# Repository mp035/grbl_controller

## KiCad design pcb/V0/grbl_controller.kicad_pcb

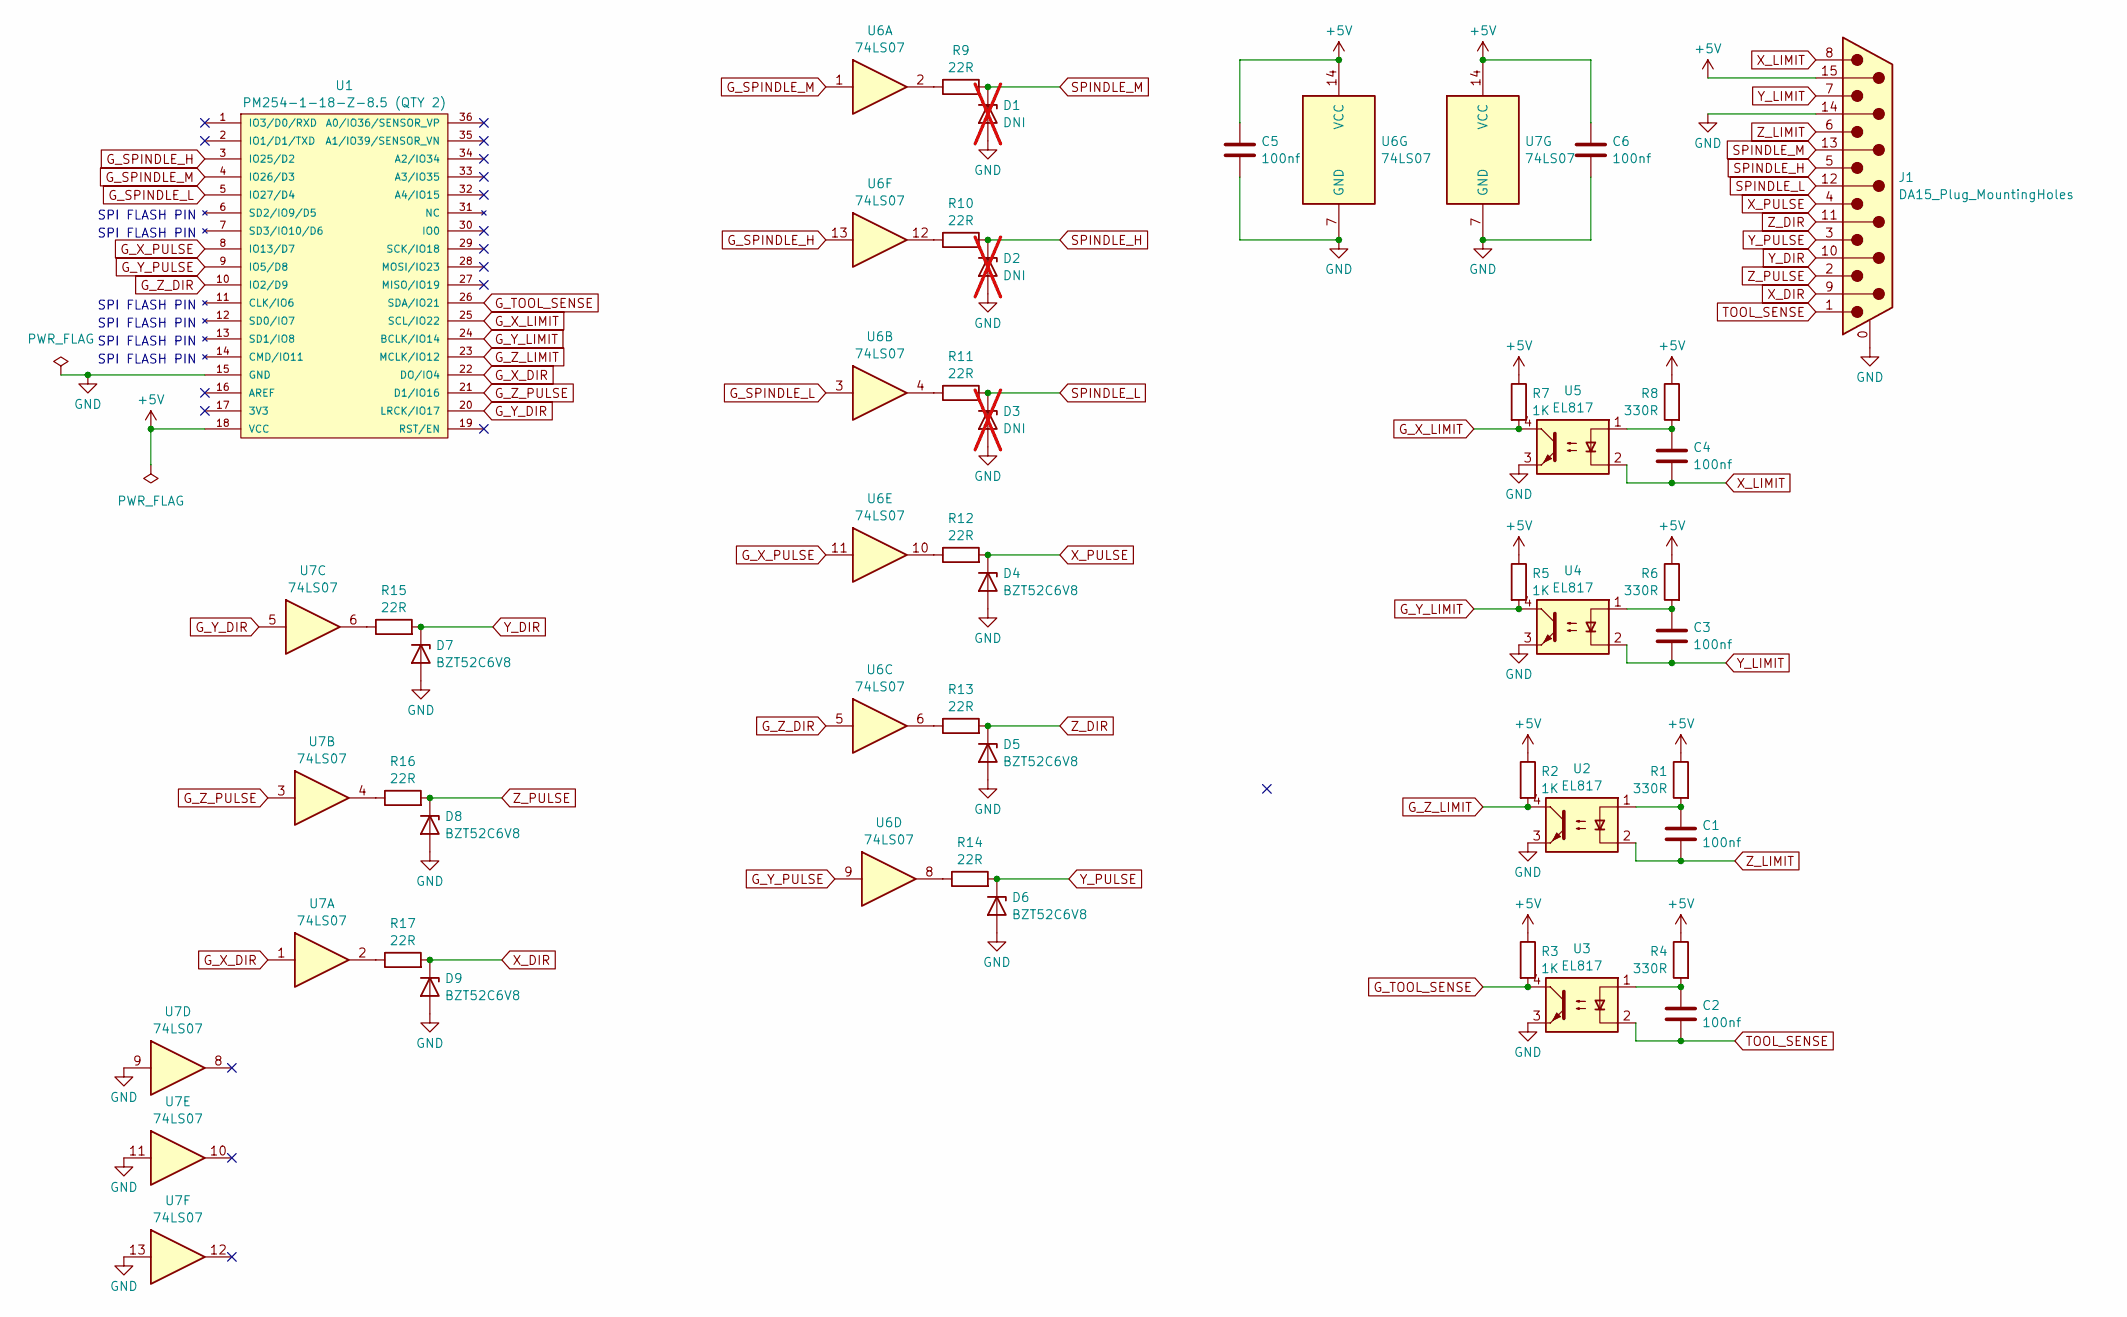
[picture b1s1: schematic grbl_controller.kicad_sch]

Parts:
C1, C2, C3, C4, C5, C6: 100nf; C_0805_2012Metric
D1, D2, D3: DNI; D_SOD-123; not fitted
D4, D5, D6, D7, D8, D9: BZT52C6V8; D_SOD-123
J1: DA15_Plug_MountingHoles; DSUB-15_Male_Horizontal_P2.77x2.84mm_EdgePinOffset9.90mm_Ho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; MPN L717SDA15P1ACH4R
R1, R4, R6, R8: 330R; R_0805_2012Metric
R2, R3, R5, R7: 1K; R_0805_2012Metric
R9, R10, R11, R12, R13, R14, R15, R16, R17: 22R; R_0805_2012Metric
U1: PM254-1-18-Z-8.5 (QTY 2); firebeetle_esp32
U2, U3, U4, U5: EL817; DIP-4_W7.62mm
U6, U7: 74LS07; SOIC-14_3.9x8.7mm_P1.27mm

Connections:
+5V: C5.1, C6.1, J1.15, R1.1, R2.1, R3.1, R4.1, R5.1, R6.1, R7.1, R8.1, U1.18 (VCC), U6.14 (VCC), U7.14 (VCC)
GND: C5.2, C6.2, D1.2 (A), D2.2 (A), D3.2 (A), D4.2 (A), D5.2 (A), D6.2 (A), D7.2 (A), D8.2 (A), D9.2 (A), J1.0 (PAD), J1.14, U1.15 (GND), U2.3, U3.3, U4.3, U5.3, U6.7 (GND), U7.7 (GND), U7.9, U7.11, U7.13
G_SPINDLE_H: U1.3 (IO25/D2), U6.13
G_SPINDLE_L: U1.5 (IO27/D4), U6.3
G_SPINDLE_M: U1.4 (IO26/D3), U6.1
G_TOOL_SENSE: R3.2, U1.26 (SDA/IO21), U3.4
G_X_DIR: U1.22 (DO/IO4), U7.1
G_X_LIMIT: R7.2, U1.25 (SCL/IO22), U5.4
G_X_PULSE: U1.8 (IO13/D7), U6.11
G_Y_DIR: U1.20 (LRCK/IO17), U7.5
G_Y_LIMIT: R5.2, U1.24 (BCLK/IO14), U4.4
G_Y_PULSE: U1.9 (IO5/D8), U6.9
G_Z_DIR: U1.10 (IO2/D9), U6.5
G_Z_LIMIT: R2.2, U1.23 (MCLK/IO12), U2.4
G_Z_PULSE: U1.21 (D1/IO16), U7.3
unnamed: C1.1, R1.2, U2.1
unnamed: C2.1, R4.2, U3.1
unnamed: C3.1, R6.2, U4.1
unnamed: C4.1, R8.2, U5.1
unnamed: R9.1, U6.2
unnamed: R10.1, U6.12
unnamed: R11.1, U6.4
unnamed: R12.1, U6.10
unnamed: R13.1, U6.6
unnamed: R14.1, U6.8
unnamed: R15.1, U7.6
unnamed: R16.1, U7.4
unnamed: R17.1, U7.2
SPINDLE_H: D2.1 (K), J1.5, R10.2
SPINDLE_L: D3.1 (K), J1.12, R11.2
SPINDLE_M: D1.1 (K), J1.13, R9.2
TOOL_SENSE: C2.2, J1.1, U3.2
X_DIR: D9.1 (K), J1.9, R17.2
X_LIMIT: C4.2, J1.8, U5.2
X_PULSE: D4.1 (K), J1.4, R12.2
Y_DIR: D7.1 (K), J1.10, R15.2
Y_LIMIT: C3.2, J1.7, U4.2
Y_PULSE: D6.1 (K), J1.3, R14.2
Z_DIR: D5.1 (K), J1.11 (P111), R13.2
Z_LIMIT: C1.2, J1.6, U2.2
Z_PULSE: D8.1 (K), J1.2, R16.2

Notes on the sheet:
SPI FLASH PIN

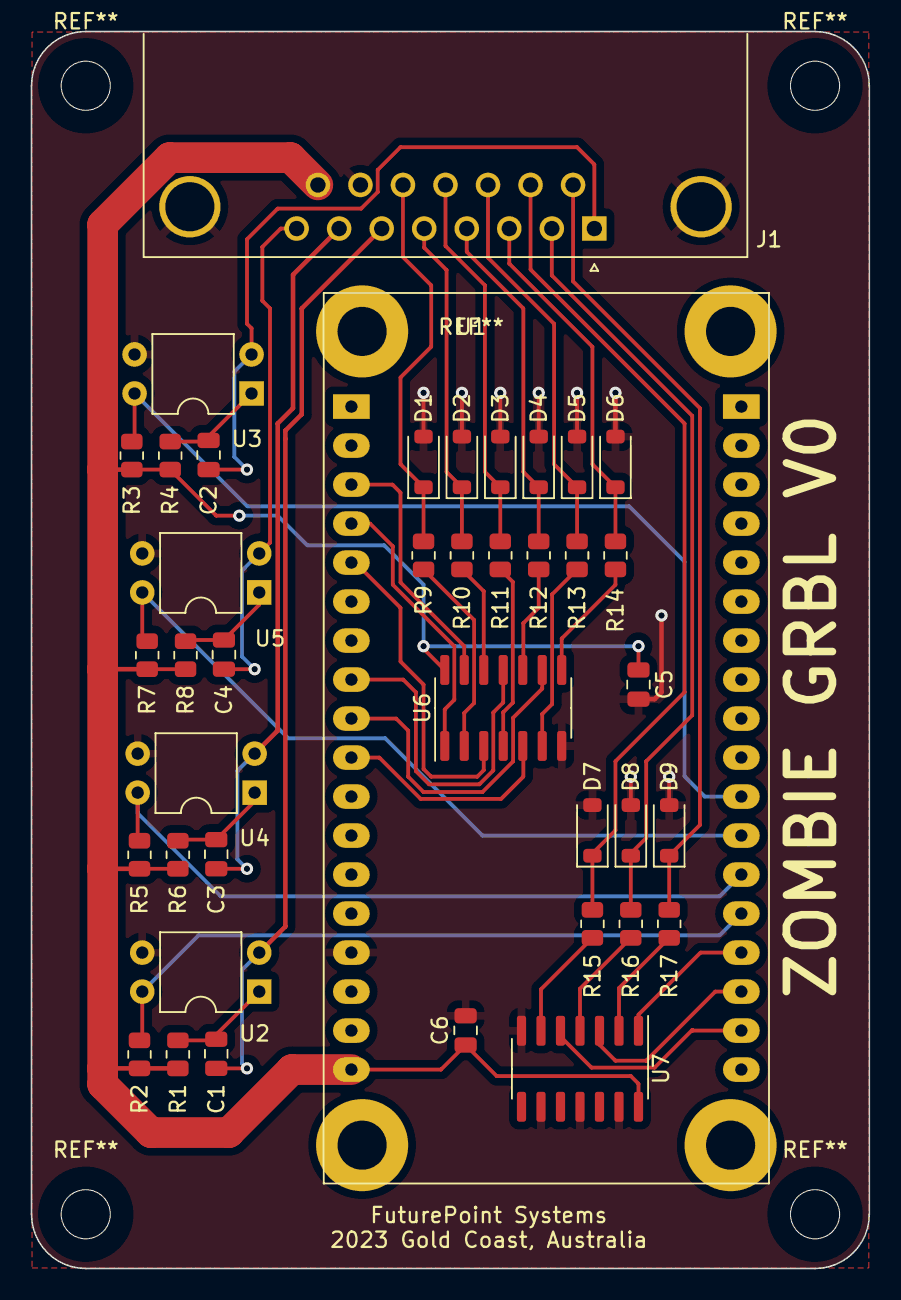
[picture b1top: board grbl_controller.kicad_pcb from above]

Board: 2 copper layers, 54.6 x 80.6 mm, 40 parts (0 on the bottom side), 41 nets.

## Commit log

2023-10-02 Initial PCB commit.
2023-10-02 Finished PCB layout.
2023-10-02 Removed lock file.
2023-10-05 Updated firebeetle mounting holes.
